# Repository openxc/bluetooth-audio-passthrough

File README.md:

Bluetooth Audio Accessory
=========================

This repository is a part of the [OpenXC][] project.

This repository contains the documentation and open source design files for an
example OpenXC hardware accessory, the Bluetooth Audio accessory, originally
created by Ford.

There is a [gallery of
photos](https://plus.google.com/photos/108408483770573977605/albums/5989364910333751905)
of the prototype accessory.

### Description

The Bluetooth Audio Passthrough is an audio-capable Bluetooth chipset, powered
and configurable over USB. The Passthrough uses a Bluegiga WT-32 Bluetooth
module, which is capable of running several different Bluetooth profiles in the
Bluetooth 2.1 standard (and even multiple profiles in parallel). By default, the
BT Passthrough will appear as an A2DP audio sink - an audio endpoint that can
wirelessly stream audio from a cellphone music player to a car Aux input.

### Features

* Supports many Bluetooth protocols out of the box: SPP, DUN, OBEX OPP, HFP
    (v.1.5) A2DP, AVRCP, DID and HID
* Configurable over USB using easy-to-read commands
* 2 output channels (stereo), one input channel (mono)
* Provides a 2.7v microphone bias
* Output headphone amplifier capable of driving up to 105mW per channel

Documents
---------

The schematics, board layout, BOM and testing results are in the `schematics`
directory of this repository.

The schematics were created with Eagle, and are also available as PNGs.

### Assembly Files

The assembly files are in the `fabrication` subfolder, including the board
layout DXF and and archive of all assembly files:

 * .top  - Top Copper Layer
 * .bot  - Bottom Copper Layer
 * .smt - Top Soldermask
 * .slk - Top Silkscreen
 * .tsp - Top Solderpaste
 * .smb - Bottom Soldermask
 * .bsk - Bottom Silkscreen
 * .bsp - Bottom Solderpaste
 * .oln - PCB Outline
 * .drd - Excellon Drill Data
 * .drl - Basic Drill tool information
 * .dri - Extended Drill tool information

Details
-------

### Block diagram

### Parts Layout

### Inputs/Outputs

* JP1 - Serial RX and TX lines - if the USB-Serial interface is not working,
    the TX and RX serial lines can be accessed from this header.
* JP2 - Power - Access to the +3.3V and Ground power rails.
* JP3 - USB CTS and RTS - Access to the hardware flow control lines provided
    by the FT232RL USB to serial IC.
* JP4 - Bluetooth CTS and RTS - Access to the hardware flow control lines on
    the WT32 adapter. Can be used with JP3 to enable hardware flow control.
* J3 - SPI programming interface - If the firmware on the WT32 needs to be
    updated from iWrap 4, this interface can be used.
* J2 (the Headphone Jack) - This is a 4 pole TRRS connector, which can be used
    for 2 output channels and 1 input channel. A standard 3-pin TRS headphone
    cable can be used, and the microphone input will be unused.
    * Pin 1 (tip) - Out Left
    * Pin 2 (ring 1) - Out Right
    * Pin 3 (ring 2) - Ground
    * Pin 4 (shield) - Microphone Input

Usage:
------

### How to use

1. Plug the Bluetooth Audio Accessory into the Dock
1. Connect the short 4-pin 1/8" TRRS cable to the audio jack on the Accessory
1. Connect the other end of the TRRS cable into the dock
1. Plug a 1/8" headset or 1/8" extension cable into the dock
1. On a smartphone or tablet, search for Bluetooth devices
1.  A "WT-32" device should appear. Pair with it. No PIN code should be
    necessary, but "0000" can be used.
1.  Once pairing is complete, connect to the WT-32 device
1. The LED on the Bluetooth Audio Accessory should turn green and the Bluetooth
    host should now play audio through the device.

### How to program

Upon receiving a Bluetooth Audio Accessory from the factory, a quick
configuration step will be required:

1. Connect the Accessory directly into the USB port of a PC
1. The accessory should appear as a serial device (/dev/ttyUSBX in linux, COMX
   in windows, /dev/tty.usbserial-xxxxxxxx in OSX).
1. In a terminal application, open the serial port with baud 115200 and no
   hardware flow control.
1. Type ```RESET``` and press enter. The Accessory should respond with the
   iWrap firmware version.
1. Type the following commands, pressing enter after each line:

```
SET BT SSP 3 0
SET BT AUTH * 0000
SET PROFILE A2DP SINK
SET PROFILE AVRCP CONTROLLER
SET BT CLASS 240438
SET CONTROL GAIN D D
SET CONTROL INIT SET CONTROL GAIN D D
SET CONTROL CD 400 0
RESET
```

The device should now be ready for use as an A2DP sink. Here are a few other
popular protocols (repeat the above steps to apply):

#### A2DP Sink (Audio from Bluetooth to Speaker)

```
SET PROFILE A2DP SINK

SET PROFILE AVRCP CONTROLLER

SET BT CLASS 240438
```

#### A2DP Source (Audio from Microphone to Bluetooth)

```
SET PROFILE A2DP SOURCE

SET PROFILE AVRCP TARGET

SET BT CLASS 280428
```

#### HFP - Hands Free Protocol (Act like Bluetooth Headset)

```
SET BT SSP 3 0
SET BT AUTH * 0000
SET PROFILE HFP ON
SET BT CLASS 200404
```

### Known issues

#### v0.1

* Audio output noise
    * Power supply - The audio output is fairly sensitive to power supply
        noise. The +5V USB power supply is filtered, but very noisy USB busses
        can still produce audible pops and buzzes
    * Bluetooth - The headphone amplifier is somewhat sensitive to Bluetooth
        energy. If the connected tablet or cell phone is held very closely to
        the BT Passthrough, cellular and/or Bluetooth noise will be induced into the
        audio output. Try not to rest any cellular devices immediately against
        the Passthrough.
* Audio output level - The default gain on the WT32 chipset is fairly
    conservative. To increase the default gain, connect the BT Passthrough to a PC. It
    should appear as a serial device. Connect to that serial device at 115200
    baud, and send the following commands:

```
RESET

SET CONTROL GAIN D D

SET CONTROL INIT SET CONTROL GAIN D D

RESET
```

Try adjusting the 0xD parameter above (valid range is 0 - 17 in hexadecimal, see
the WT-32 manual). In testing, a gain of 0xD is the highest that a pair of 64
ohm headphones would tolerate before distortion.

Design details:
---------------

### Bluetooth Chipset

The WT-32 was selected as a prototype-friendly Bluetooth Audio chipset. It was
the only chipset available from distributors like SparkFun that had full, native
audio support. Advantages:

* Simple serial command protocol
* Many built-in Bluetooth protocols
* Built-in microphone pre-amplifier with software-adjustable gain
* software-adjustable output gain as well

The basic WT-32 design is very strongly based from its [Evaluation
Board](http://www.digikey.com/product-search/en/rf-if-and-rfid/rf-evaluation-and-development-kits-boards/3539644?k=WT32).
The WT32 documentation is available in the Documentation directory.

### Configuration Interface

The WT-32 is configured by a serial UART at 115200 baud. This is exposed via
USB using an industry-standard [FTDI
FT232RL](http://www.ftdichip.com/Support/Documents/DataSheets/ICs/DS_FT232R.pdf)
USB to serial converter IC. The chip requires few external components - each
power rail is decoupled with 0.1uF capacitors, TX and RX LEDs are included, and
the UART is protected from excess current through RX and TX resistors R1 and R2.
USB signals require high speed PCB routing to avoid signal integrity issues,
since the bitrates are high (11Mbps - 480Mbps). Unfortunately with a 2 layer
PCB, the trace widths required to obtain the ideal 90 ohm differential impedance
for a USB line would be unfeasibly wide. To compensate for this fact, the USB
connector was located extremely close (~300 mils) to the FTDI 232RL USB pins.

The WT-32 also has an ICSP header if future firmware updates are desired.
Current WT-32 modules will ship with either iWrap4 or iWrap5 firmware, both of
which contain the necessary configurations and protocols needed by the
accessory. Upgrading shouldn't be necessary, but is possible using the SPI bus
exposed by J3. See the WT32 documentation for firmware upgrade procedures.

### Power

A single Low Dropout linear regulator is used to step the +5V USB power down to
the 3.3V required by the Bluetooth module. IC5 preforms this task, providing up
to 1.6A of current (far more than is necessary). The power is filtered in two
places. Immediately after entering via the USB connector, power is passed
through inductor L3 with filtering capacitors C12 and C5. This is from the
FT232RL reference design. An additional filtering stage separates the normal
+3.3V rail from the +3.3V used by the analog audio circuitry. Analog power is
run through inductor L4 and decoupled by C16 in an attempt to remove additional
transients caused by the power draw of the WT32.

A DC midpoint is also required by the output amplifier. Since the amplifier is
a single-ended device (no negative power rail is available), a midpoint is
required to properly bias / center the audio signal before amplification. This
is generated using a rudimentary resistor divider of R6 and R7. Excess DC
midpoint current can unbalance the amplifier, but with the low input impedance
of the output amplifier, this shouldn't be an issue. If the DC midpoint becomes
unbalanced, or if more ground filtering is desired, consider buffering the
DC_MID signal with an opamp.

### Analog Microphone Input

The microphone input receives it's signal from pin 4 of the TRRS audio
connector. IC2 provides a 2.7V microphone bias for the microphone in a
connected headset. The WT32 contains a microphone bias output, but the
reference schematic recommends using an additional Low Dropout Regulator (IC2)
instead. The LDO provides additional power filtering for the microphone bias,
which is an extremely noise-sensitive signal for an electret microphone element.
This circuit assumes a microphone element with an impedance in the 1k - 3k range
(specifically we are matching 1K using resistor R3).

Inductors L1 and L2 and capacitors C9 and C10 attempt to filter excess high
frequency noise from the microphone. Capacitors C11 and C13 decouple the
microphone signal before connecting it to the WT32. Diodes D1 and D2 protect
the WT-32 built-in microphone preamplifier and ADC from damage due to voltage
transients by clamping the microphone signal to +3.3v and Ground. Note that
this circuit uses a shared ground for the microphone input and the headphone
output - if crosstalk between headphones and microphone becomes an issue,
consider spliting the 4-pin TRRS jack into two seperate 3-pin TRS jacks.

### Headphone / Line output

A [TI LM4808 Headphone Amplifier](http://www.ti.com/lit/ds/symlink/lm4808.pdf)
isolates the audio output from the WT32. The reference design was pulled
directly from the WT-32 evaluation board. The amplifier also converts the
differential audio output of the WT32 into a single-ended output used by most
headphones and consumer electronics. Note that output decoupling capacitors C23
and C28 are specified as Tantalum capacitors, since they lie directly in the
audio pathway and need to be robust to handle the voltage transients of plugging
and unplugging audio signals. Care must be taken to chose capacitors with a
good sonic signature, low ESR and a sufficient voltage rating.

## License

Copyright (c) 2014 Ford Motor Company

The electrical and mechanical designs in this repository are available under the
[Creative Commons Attribution 4.0
International](http://creativecommons.org/licenses/by/4.0/deed.en_US) license.

[OpenXC]: http://openxcplatform.com

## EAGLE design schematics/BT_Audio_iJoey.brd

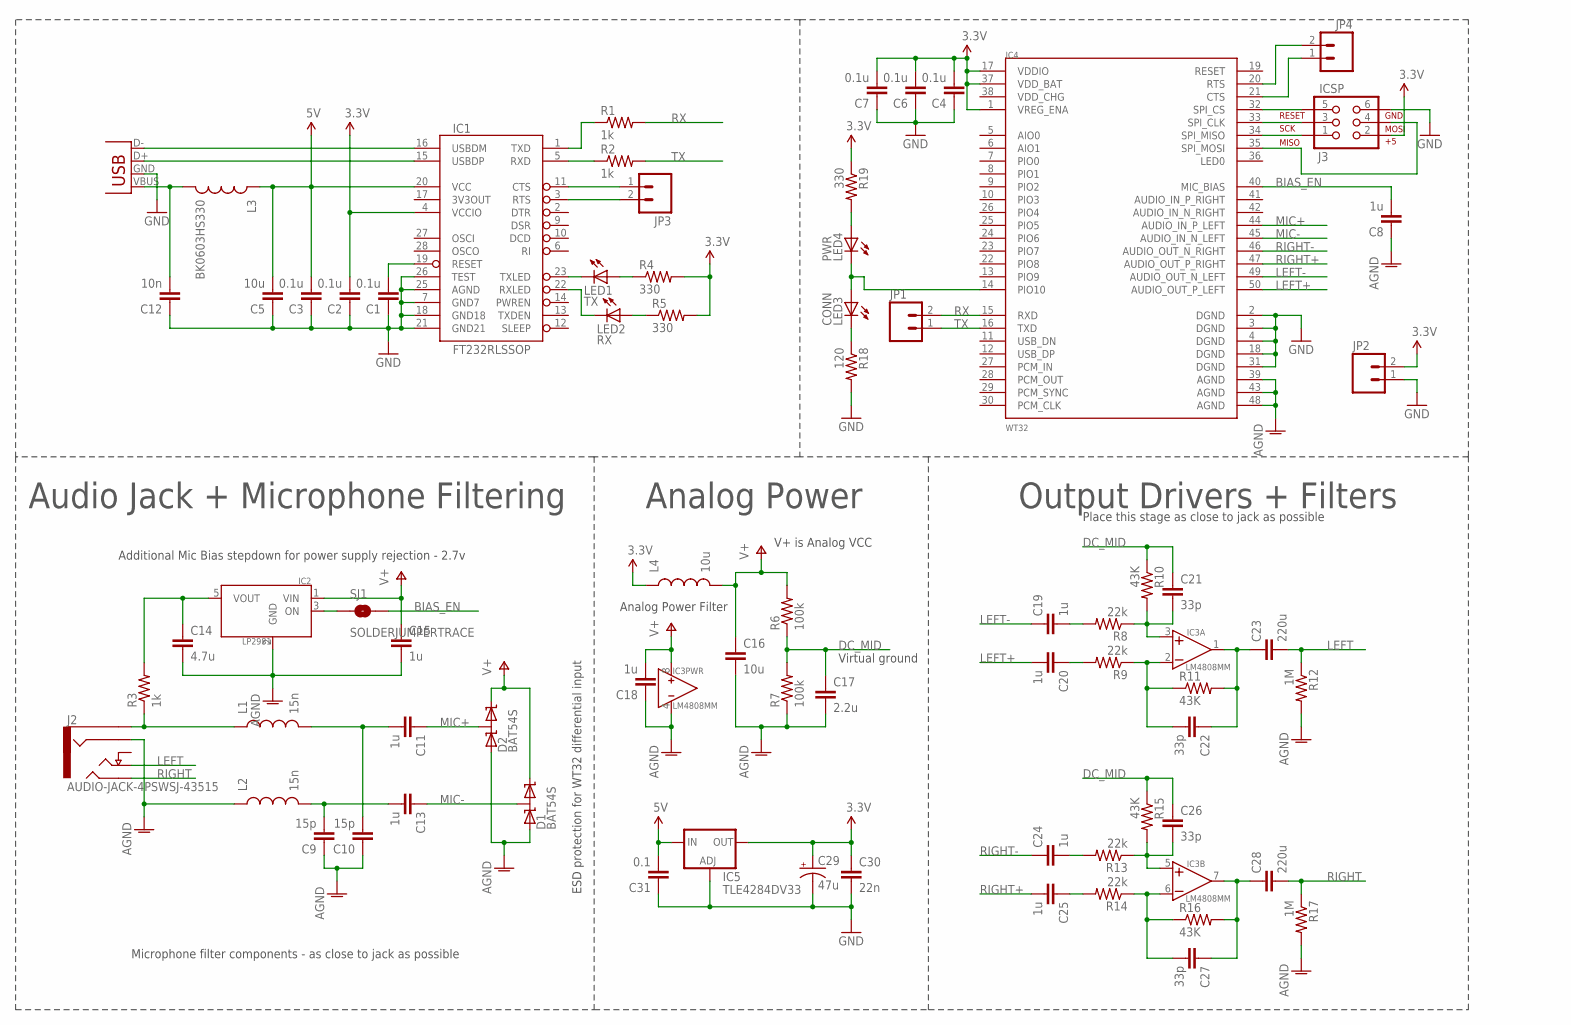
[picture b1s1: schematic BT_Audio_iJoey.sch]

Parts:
C1, C2, C3, C4, C6, C7: 0.1u; 0603-CAP
C5: 10u; 0805
C8, C11, C13, C15, C18, C19, C20, C24, C25: 1u; 0603-CAP
C9, C10: 15p; 0603-CAP
C12: 10n; 0603-CAP
C14: 4.7u; 0603-CAP
C16: 10u; 0603-CAP
C17: 2.2u; 0603-CAP
C21, C22, C26, C27: 33p; 0603-CAP
C23, C28: 220u; 1210
C29: 47u; PANASONIC_D
C30: 22n; 0603-CAP
C31: 0.1; 0603-CAP
D1, D2: BAT54S; SOT23
IC1: FT232RLSSOP; SSOP28DB
IC2: LP2981; SOT23-5
IC3: LM4808MM; SO8
IC4: WT32
IC5: TLE4284DV33; V-REG_DPACK
J1: USB-A-H
J2: AUDIO-JACK-4PSWSJ-43515; SJ-4351X
J3: ICSP; 2X3
JP1, JP2, JP3, JP4: M02PTH; 1X02
L1, L2: 15n; 0603
L3: BK0603HS330; 0603
L4: 10u; 0603
LED1: TX; LED-0603
LED2: RX; LED-0603
LED3: CONN; LED-0603
LED4: PWR; LED-0603
R1, R2, R3: 1k; 0603-RES
R4, R5, R19: 330; 0603-RES
R6, R7: 100k; 0603-RES
R8, R9, R13, R14: 22k; 0603-RES
R10, R11, R15, R16: 43K; 0603-RES
R12, R17: 1M; 0603-RES
R18: 120; 0603-RES
SJ1: SOLDERJUMPERTRACE; SJ_2S-TRACE

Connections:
3.3V: C2.2, C4.2, C6.2, C7.2, C29.+, C30.1, IC1.4 (VCCIO), IC4.1 (VREG_ENA), IC4.17 (VDDIO), IC4.37 (VDD_BAT), IC5.4 (OUT), J3.2, JP2.2, L4.1, R4.2, R5.2, R19.1
5V: C3.2, C5.2, C31.2, IC1.20 (VCC), IC5.3 (IN), L3.1
AGND: C8.1, C9.1, C10.1, C14.2, C15.2, C16.2, C17.2, C18.1, D1.1 (AN), D2.1 (AN), IC2.2 (GND), IC3.4 (-V), IC4.39 (AGND), IC4.43 (AGND), IC4.48 (AGND), J2.4 (RING2), L2.1, R7.1, R12.2, R17.2
BIAS: C14.1, IC2.5 (VOUT), R3.2
BIAS_EN: C8.2, IC4.40 (MIC_BIAS), SJ1.2
DC_MID: C17.1, C21.1, C26.1, R6.1, R7.2, R10.1, R15.1
GND: C1.1, C2.1, C3.1, C4.1, C5.1, C6.1, C7.1, C12.1, C29.-, C30.2, C31.1, IC1.7 (GND7), IC1.18 (GND18), IC1.21 (GND21), IC1.25 (AGND), IC1.26 (TEST), IC4.2 (DGND), IC4.3 (DGND), IC4.4 (DGND), IC4.18 (DGND), IC4.31 (DGND), IC5.1 (ADJ), J1.GND (VBUS), J3.6, JP2.1, R18.2
LEFT: C23.2, J2.2 (TIP), R12.1
LEFT+: C20.2, IC4.50 (AUDIO_OUT_P_LEFT)
LEFT-: C19.1, IC4.49 (AUDIO_OUT_N_LEFT)
MIC+: C11.1, D2.3 (COM), IC4.44 (AUDIO_IN_P_LEFT)
MIC-: C13.1, D1.3 (COM), IC4.45 (AUDIO_IN_N_LEFT)
unnamed: IC1.15 (USBDP), J1.D+ (D-)
unnamed: IC1.16 (USBDM), J1.D- (D+)
unnamed: IC4.33 (SPI_CLK), J3.3
unnamed: C1.2, IC1.19 (RESET)
unnamed: C12.2, J1.VBUS (GND), L3.2
unnamed: IC4.32 (SPI_CS), J3.5
unnamed: IC1.5 (RXD), R2.1
unnamed: IC1.1 (TXD), R1.1
unnamed: IC4.34 (SPI_MISO), J3.1
unnamed: IC1.23 (TXLED), LED1.C
unnamed: IC1.22 (RXLED), LED2.C
unnamed: LED2.A, R5.1
unnamed: LED1.A, R4.1
unnamed: IC4.35 (SPI_MOSI), J3.4
unnamed: C9.2, C13.2, L2.2
unnamed: J2.1 (SLEEVE), L1.1, R3.1
unnamed: C10.2, C11.2, L1.2
unnamed: C22.2, IC3.2 (-), R9.1, R11.1
unnamed: C20.1, R9.2
unnamed: C21.2, IC3.3 (+), R8.1, R10.2
unnamed: C19.2, R8.2
unnamed: C22.1, C23.1, IC3.1 (O), R11.2
unnamed: C27.2, IC3.6 (-), R14.1, R16.1
unnamed: C25.1, R14.2
unnamed: C26.2, IC3.5 (+), R13.1, R15.2
unnamed: C24.2, R13.2
unnamed: C27.1, C28.1, IC3.7 (O), R16.2
unnamed: IC2.3 (ON), SJ1.1
unnamed: IC1.11 (CTS), JP3.1
unnamed: IC1.3 (RTS), JP3.2
unnamed: IC4.21 (CTS), JP4.1
unnamed: IC4.20 (RTS), JP4.2
unnamed: IC4.14 (PIO10), LED3.A, LED4.C
unnamed: LED3.C, R18.1
unnamed: LED4.A, R19.2
RIGHT: C28.2, J2.3 (RING1), R17.1
RIGHT+: C25.2, IC4.47 (AUDIO_OUT_P_RIGHT)
RIGHT-: C24.1, IC4.46 (AUDIO_OUT_N_RIGHT)
RX: IC4.15 (RXD), JP1.2, R1.2
TX: IC4.16 (TXD), JP1.1, R2.2
V+: C15.1, C16.1, C18.2, D1.2 (CAT), D2.2 (CAT), IC2.1 (VIN), IC3.8 (+V), L4.2, R6.2

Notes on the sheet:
Place this stage as close to jack as possible
Analog Power
Audio Jack + Microphone Filtering
Output Drivers + Filters
Microphone filter components - as close to jack as possible
Additional Mic Bias stepdown for power supply rejection - 2.7v
Virtual ground
Analog Power Filter
V+ is Analog VCC
ESD protection for WT32 differential input

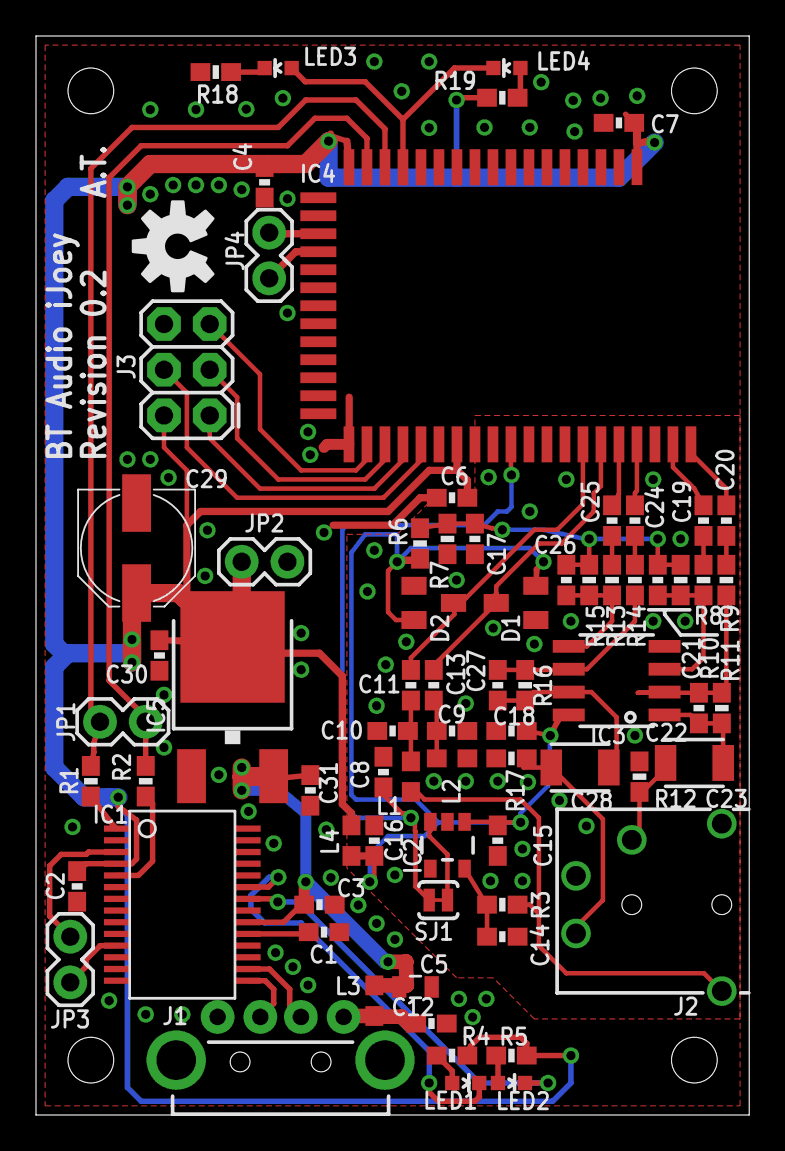
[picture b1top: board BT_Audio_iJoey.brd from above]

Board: 2 copper layers, 39.6 x 59.9 mm, 76 parts (0 on the bottom side), 53 nets.

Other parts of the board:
DRILEGEND: DRILEGEND
U$1: A5L-LOC
U$2: OSHW-LOGO-M

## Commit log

2013-04-19 Initial commit.
2013-04-19 Clean up README and clarify a few things.
2013-04-19 Update instructions for enabling HFP.
2013-09-18 Remove extra spaces.
2013-09-18 Add verification tests as plain text.
2014-03-11 Add license and update README for release.
2014-03-11 Add a link to a gallery of photos.

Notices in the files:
parts and their libraries:
SparkFun-Connectors: Licensing: CC v3.0 Share-Alike You are welcome to use this library for commercial purposes.
